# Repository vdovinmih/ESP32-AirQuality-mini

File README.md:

# ESP32-AirQuality-mini
AirQuality zigbee mini sensor ESP32

Цели и задачи устройства:
1. измерять температуру, влажность, и показатель качества воздуха (TVOС)
2. по протоколу zigbee передавать эти показания в систему умного дома на основе z2m
3. [опция] выступать роутером в zigbee сети
4. [опция] передавать измеренные значения напрямую в устройства одной zigbee сети минуя координатор и сервер умного дома

Основные комплектующие: 
1. ESP32- C6/H2 SuperMini 
https://aliexpress.ru/item/1005006907067134.html?spm=a2g2w.orderdetail.0.0.60bb4aa6OtokH4&sku_id=12000041762699861
https://aliexpress.ru/item/1005008148472502.html?sku_id=12000043993594567&spm=a2g2w.productlist.search_results.0.532a1736lb0FJ2
https://github.com/Zektopic/esp32-h2-supermini-kicad?ysclid=memrikceaz898473666
* H2 
https://www.espboards.dev/esp32/esp32-h2-super-mini/
* C6 
https://www.espboards.dev/esp32/esp32-c6-super-mini/

3. Датчик температуры и влажности AHT10 (i2c)
https://aliexpress.ru/item/1005008699139931.html?sku_id=12000046300583727&spm=a2g2w.productlist.search_results.1.28c04050xA3ERq

4. AGS10 Модуль обнаружения газа (i2c)
https://aliexpress.ru/item/1005008593136272.html?sku_id=12000048412147624&spm=a2g2w.productlist.search_results.1.490f4050ZTz7pN

5. [опция] на площадки модуля B+ B- опционально можно подключить 3.7в LiIon АКБ совмещённый с модулем защиты
https://aliexpress.ru/item/1005004304618610.html?sku_id=12000028691739753&spm=a2g2w.productlist.search_results.1.18de2d01bsl4up

на модули датчиков питание 3.3в подаётся с ESP32-H2, +2 пина i2c, я использовал (H2 модуль) 13, 14. Но 13 нога висит в паралель с диодом. Лучше использовать другую пару например 11,12
 
Питание устройства:
1. Интегрированный на ESP32 модуле разъём usb-c
2. пара клемм на 12 вольт (при наличии преобразователя 12в -> 5в), опционально делитель для измерения
3. для измерения напряжения батареи нужен делитель. 50/50
4.

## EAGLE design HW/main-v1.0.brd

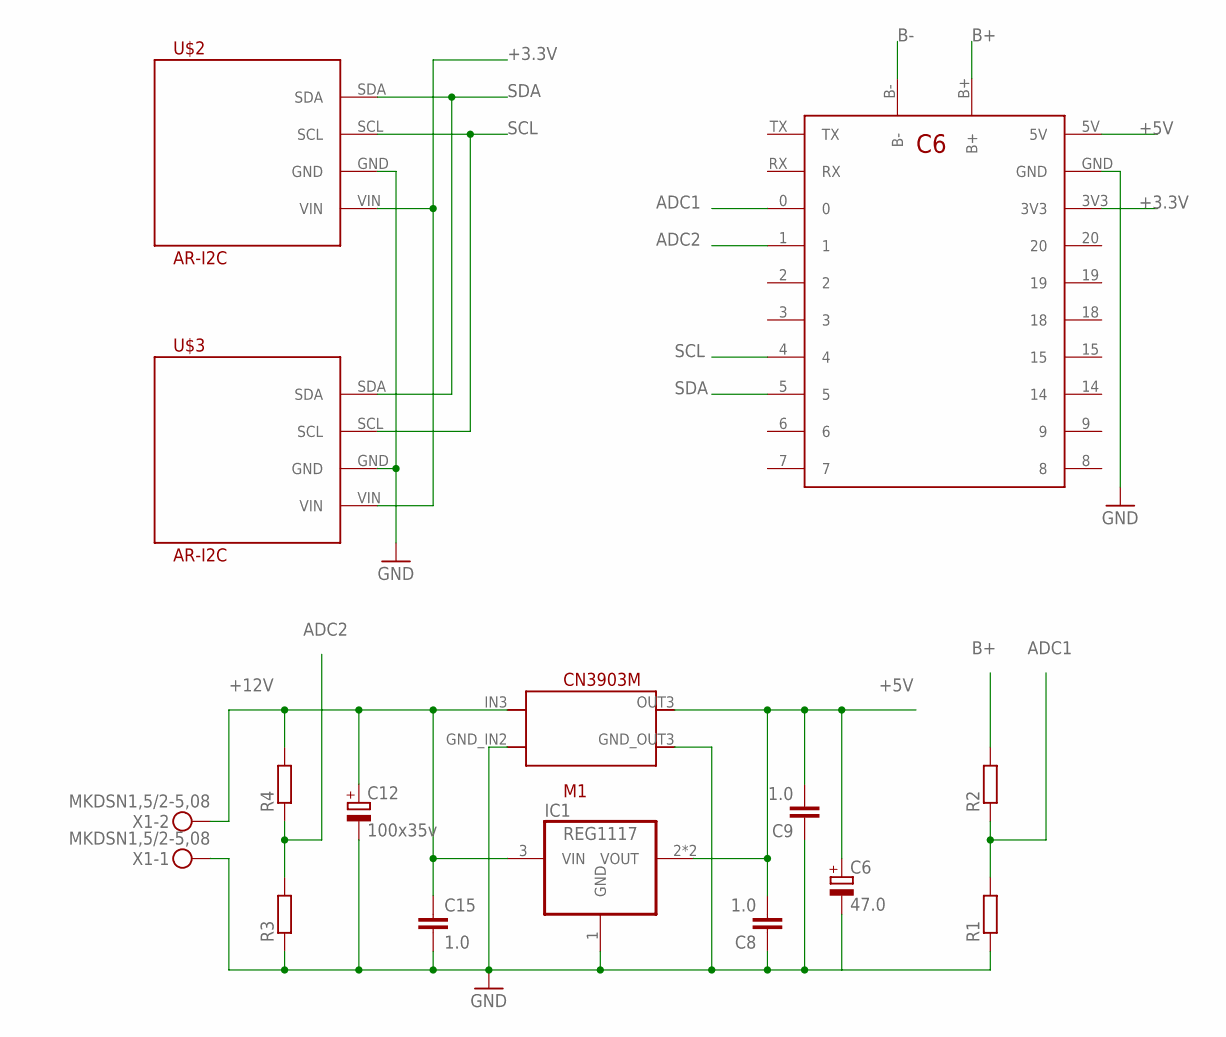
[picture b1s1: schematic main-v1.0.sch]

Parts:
C6: 47.0; SMC_B
C8, C9: 1.0; C0805
C12: 100x35v; SMC_E
C15: 1.0; C1206
IC1: REG1117; SOT223
M1: CN3903M
R1, R2, R3, R4: R-EU_R0603; R0603
U$1: ESP32-C6-SM; ESP32-C6-SUPER-MINI
U$2, U$3: AR-I2C
X1: MKDSN1,5/2-5,08

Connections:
+3.3V: U$1.3V3, U$2.VIN, U$3.VIN
+5V: C6.+, C8.2, C9.2, IC1.2 (VOUT), IC1.4 (VOUT), M1.OUT3 (OUT), U$1.5V
+12V: C12.+, C15.1, IC1.3 (VIN), M1.IN3 (IN), R4.2, X1.2
ADC1: R1.2, R2.1, U$1.0
ADC2: R3.2, R4.1, U$1.1
B+: R2.2, U$1.B+
B-: U$1.B-
GND: C6.-, C8.1, C9.1, C12.-, C15.2, IC1.1 (GND), M1.GND_IN2 (GND_IN), M1.GND_OUT3 (GND_OUT), R1.1, R3.1, U$1.GND, U$2.GND, U$3.GND, X1.1
SCL: U$1.4, U$2.SCL, U$3.SCL
SDA: U$1.5, U$2.SDA, U$3.SDA

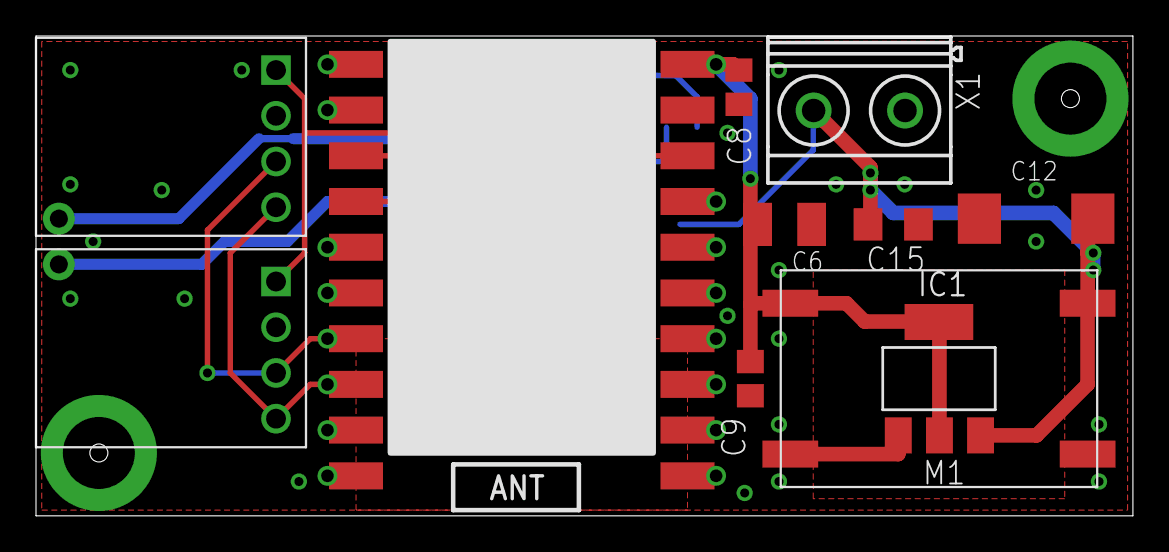
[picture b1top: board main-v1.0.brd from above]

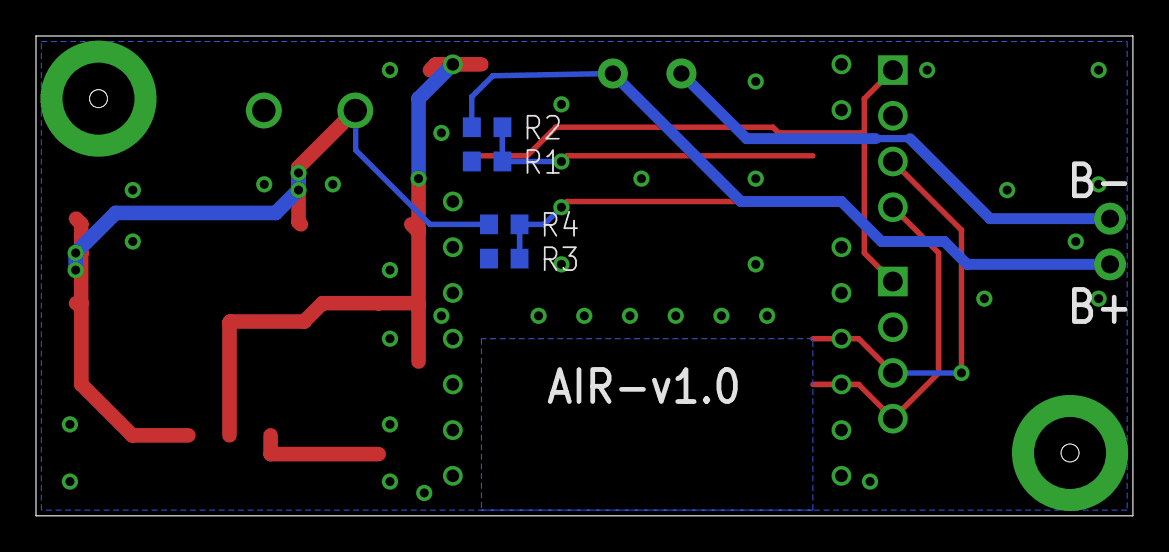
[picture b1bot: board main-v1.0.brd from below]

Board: 2 copper layers, 60.9 x 26.7 mm, 15 parts (4 on the bottom side), 9 nets.

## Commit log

2025-09-03 Add some Code
2025-09-03 move z2m converter to root
2025-10-06 PCB v1.0
2025-10-24 add esp32-c6 support
